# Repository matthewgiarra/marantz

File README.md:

# marantz
Knockoffs of old Marantz stereos

# Actual content
[P700 Pre-amp board](https://github.com/matthewgiarra/marantz/tree/main/2225/PE01) with schematics, PCB layout, renders, gerber files, and photos of the completed board. 

[Confluence page](https://matthewgiarra.atlassian.net/wiki/spaces/marantz/pages/33577/Gesundheit+Model+82+Stereophonic+Receiver+Requirements) (design concepts, system requirements, etc.)

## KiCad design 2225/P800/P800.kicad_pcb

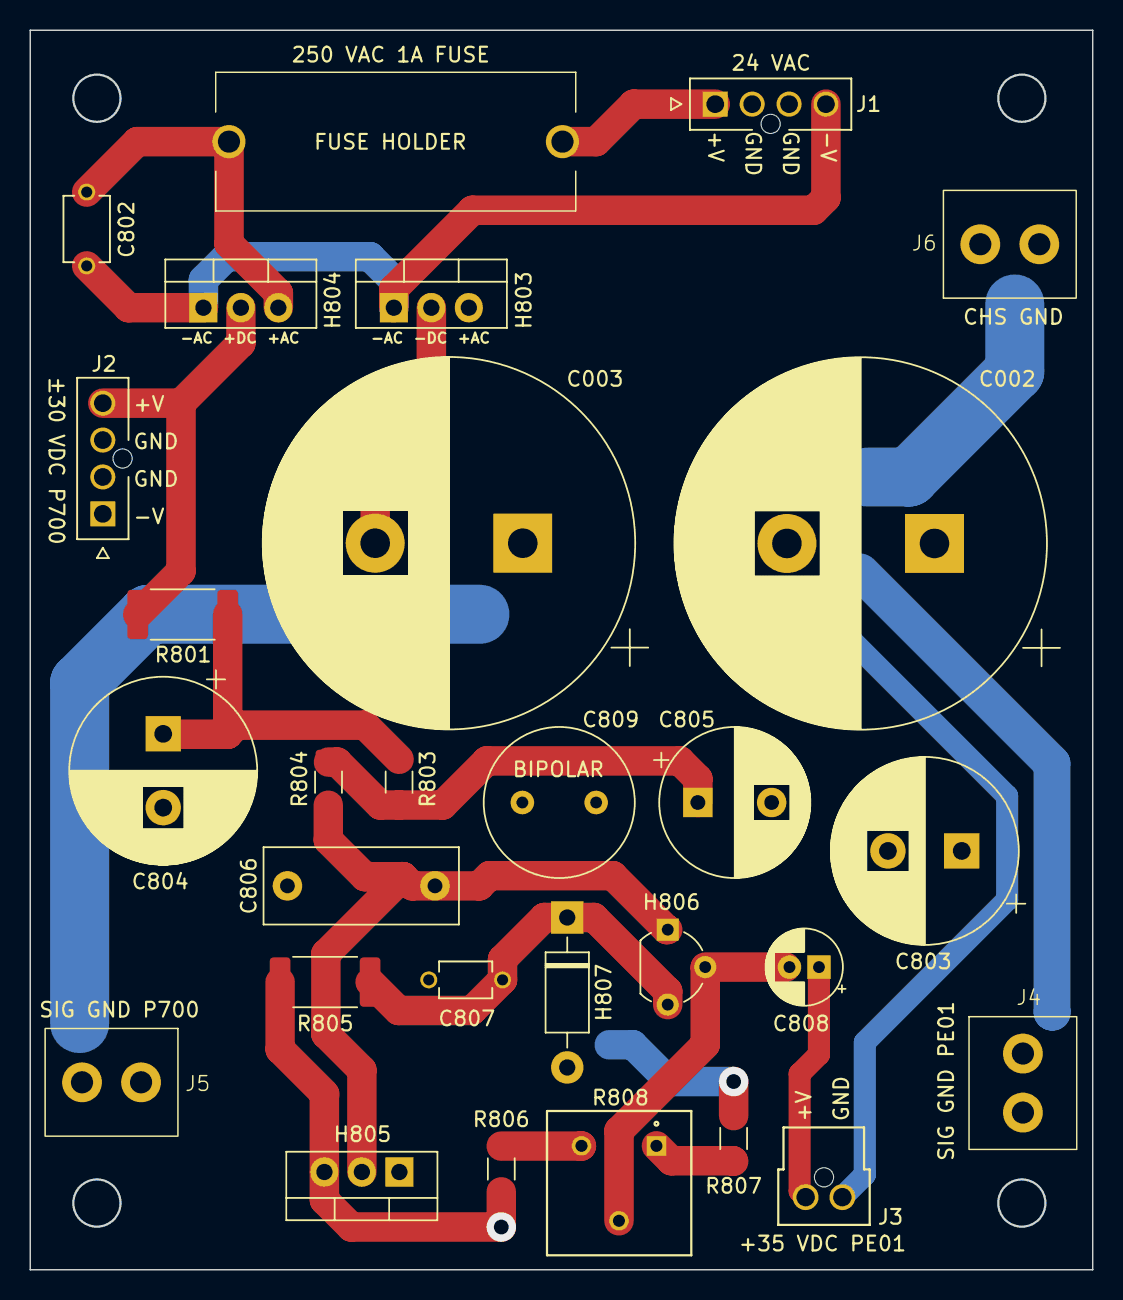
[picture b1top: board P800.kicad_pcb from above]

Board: 4 copper layers, 71.9 x 83.9 mm, 30 parts (0 on the bottom side), 14 nets.

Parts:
C002, C003: 6800u; CP_Radial_D25.0mm_P10.00mm_SnapIn
C802: 0.01u; cap_ceramic_RDER72H103K1M1H03A
C803, C804: 470u; CP_Radial_D12.5mm_P5.00mm
C805: 100u; CP_Radial_D10.0mm_P5.00mm
C806: 0.047u; C_Rect_L13.0mm_W5.0mm_P10.00mm_FKS3_FKP3_MKS4
C807: 0.04u; cap_ceramic_RCER71H473K0M1H03A
C808: 3.3u; CP_Radial_D5.0mm_P2.00mm
C809: 470u; C_Radial_D10.0mm_H20.0mm_P5.00mm
F1: Fuse 1A 250V; fuse_holder_0PTF0078P
H803: MBRF10150CTR; TO-220-3_Vertical
H804: MBRF10150CT; TO-220-3_Vertical
H805: TIP41C; TO-220-3_Vertical
H806: KSC2383; TO-92_Wide
H807: 1N4744; D_DO-41_SOD81_P10.16mm_Horizontal
HS1: Heatsink; heatsink_577202B00000G
J1, J2: Conn_01x04; molex_nanofit_4-pos_header_vert_1053091204
J3: Conn_01x02; molex_nanofit_2-pos_header_vert_1053091302
J4, J5, J6: Conn_01x01; Metz_Connect_1pos_terminal_360291
R801: 22; R_2512_6332Metric_Pad1.40x3.35mm_HandSolder
R803, R804: 1.5k; R_1206_3216Metric_Pad1.30x1.75mm_HandSolder
R805: 330; R_2512_6332Metric_Pad1.40x3.35mm_HandSolder
R806: 39k; R_1206_3216Metric_Pad1.30x1.75mm_HandSolder
R807: 36k; R_1206_3216Metric_Pad1.30x1.75mm_HandSolder
R808: TRIMPOT 5K; pot_3386F-1-502LF

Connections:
/+24VAC: F1.1, J1.1
/+30VDC_out: C002.1, C803.1, H804.2, J2.4, R801.1
/+35VDC_out: C808.1, H805.3 (E), J3.2, R805.2, R806.2
/-24VAC: C802.2, H803.1, H804.1, J1.4
/-30VDC_out: C003.2, H803.2, J2.1
/H805C_45V: C804.1, H805.1 (C), R801.2, R803.2
FBR AC +: C802.1, F1.2, H803.3, H804.3
GND: C002.2, C003.1, C803.2, C804.2, C805.2, C806.2, C807.2, C809.2, H807.2 (A), J1.2, J1.3, J2.2, J2.3, J3.1, J4.1, J5.1, J6.1, R807.1
unnamed: C805.1, R803.1, R804.2
unnamed: C806.1, H805.2 (B), H806.1 (C), R804.1
unnamed: C808.2, H806.2 (B), R808.2
unnamed: C807.1, C809.1, H806.3 (E), H807.1 (K), R805.1
unnamed: R806.1, R808.3
unnamed: R807.2, R808.1

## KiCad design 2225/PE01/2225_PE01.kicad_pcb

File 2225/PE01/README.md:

# Marantz 2225 Pre-Tone Amplifier PE-01 (pre-amp)
## Overview
This project recreates (i.e., knocks off) the [Marantz 2225](https://classicreceivers.com/marantz-2225) pre-tone amplifier (PE-01), as specified in the [Marantz 2225L service manual](https://www.manualslib.com/manual/907153/Marantz-2225l.html), using modern and readily-available components. Our custom board is designed to function as a drop-in replacement for the original device. We [selected components](https://docs.google.com/spreadsheets/d/1S8Fiy-nARGqUnUXXbVScigvOsDpP3ZsTfdl-bGImHVc/edit?usp=sharing) that meet or exceed the specifications from the service manual, which were experimentally verified by measuring values of components sourced from a vintage PE-01. When discrepancies were discovered between the service manual's component specifications and physical measurements of vintage components, we prioritized the physical measurements. The PCB layout was modified as necessary to accommodate the physical dimensions of our chosen components, and uses a four-layer PCB rather than the single layer of the original product. We used KiCad for design, and validated functionality via SPICE simulation prior to manufacturing. Quantitative characterization of the physical prototype is still in progress, but the initial subjective impression is that it sounds pretty good. 

## Components
The bill of materials/components list is [here](https://docs.google.com/spreadsheets/d/1S8Fiy-nARGqUnUXXbVScigvOsDpP3ZsTfdl-bGImHVc/edit?usp=sharing).

## KiCad renders 

## Prototype board (V1.0, March 2023)

## Original PCB

## Schematic and Layout (from [Marantz 2225L service manual](https://www.manualslib.com/manual/907153/Marantz-2225l.html))

## Notes
- CE21 and CE22 should be 3.3µF, not 33µF as they're listed in the service manual.
- CE23 and CE24 are biopolar capacitors, which the service manual does not appear to indicate. 
- The first prototype board substituted the specified 7.5K resistors RE13 and RE14 with 4.7K 1% components. The reason for the substitution was to mitigate clipping observed at higher volume levels (i.e., lower input attenuation) of aux input from a Macbook headphone jack, which was about 1.5VPP.

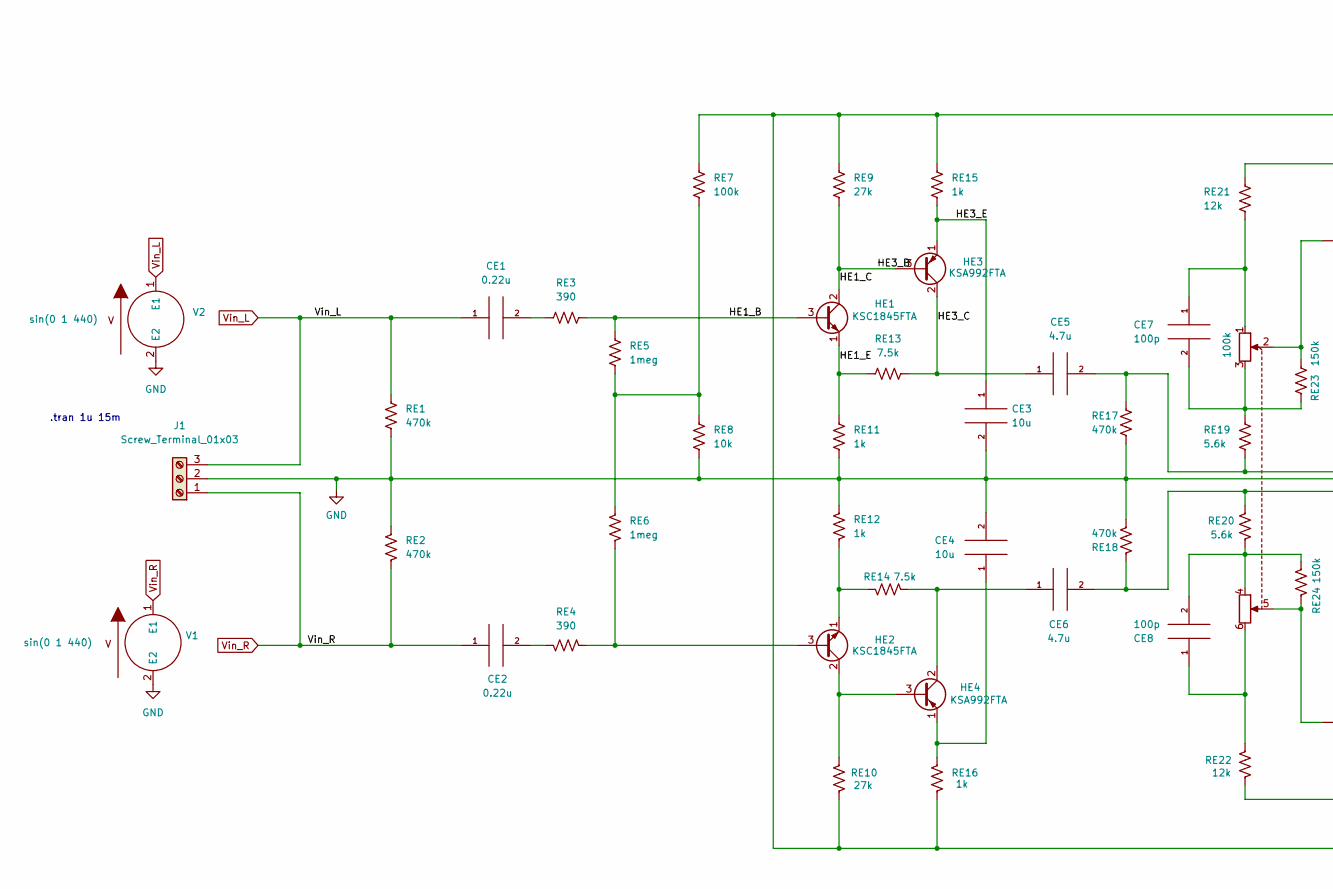
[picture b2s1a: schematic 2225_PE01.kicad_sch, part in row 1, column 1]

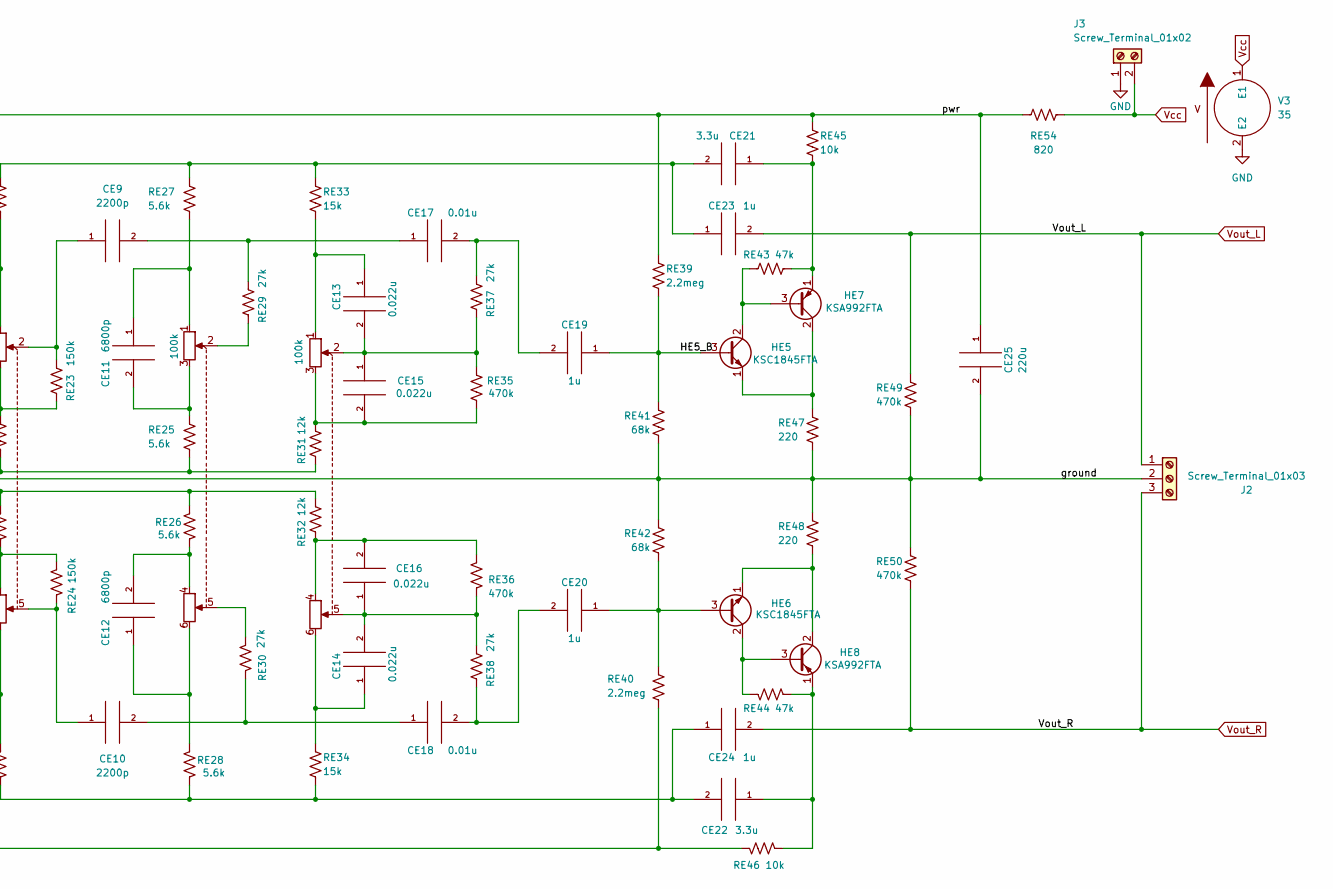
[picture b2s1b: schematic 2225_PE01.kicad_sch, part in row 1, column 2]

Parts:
CE1, CE2: 0.22u; C_Rect_L16.5mm_W4.7mm_P15.00mm_MKT
CE3, CE4: 10u; CP_Radial_D6.3mm_P2.50mm
CE5, CE6: 4.7u; CP_Radial_D5.0mm_P2.50mm
CE7, CE8: 100p; C_Disc_D7.0mm_W2.5mm_P5.00mm
CE9, CE10: 2200p; C_Rect_L7.2mm_W3.5mm_P5.00mm_FKS2_FKP2_MKS2_MKP2
CE11, CE12: 6800p; C_Rect_L7.2mm_W3.5mm_P5.00mm_FKS2_FKP2_MKS2_MKP2
CE13, CE14, CE15, CE16: 0.022u; C_Rect_L10.0mm_W4.0mm_P7.50mm_FKS3_FKP3
CE17, CE18: 0.01u; C_Rect_L9.0mm_W3.2mm_P7.50mm_MKT
CE19, CE20: 1u; CP_Radial_D5.0mm_P2.50mm
CE21, CE22: 3.3u; CP_Radial_D6.3mm_P2.50mm
CE23: 1u; C_Radial_D6.3mm_H11.0mm_P3.50mm
CE24: 1u; C_Radial_D6.3mm_H11.0mm_P2.50mm
CE25: 220u; CP_Radial_D10.0mm_P5.00mm
HE1, HE2, HE5, HE6: KSC1845FTA; TO-92_Inline
HE3, HE4, HE7, HE8: KSA992FTA; TO-92_Inline
J1, J2: Screw_Terminal_01x03; Molex_Eurostyle_39357-0003_1x03_P3.5mm_Horizontal
J3: Screw_Terminal_01x02; Molex_Eurostyle_39357-0002_1x02_P3.5mm_Horizontal
RE1, RE2, RE17, RE18, RE35, RE36, RE49, RE50: 470k; R_Axial_DIN0309_L9.0mm_D3.2mm_P12.70mm_Horizontal
RE3, RE4: 390; R_Axial_DIN0309_L9.0mm_D3.2mm_P12.70mm_Horizontal
RE5, RE6: 1meg; R_Axial_DIN0309_L9.0mm_D3.2mm_P5.08mm_Vertical
RE7: 100k; R_Axial_DIN0309_L9.0mm_D3.2mm_P12.70mm_Horizontal
RE8, RE45, RE46: 10k; R_Axial_DIN0309_L9.0mm_D3.2mm_P12.70mm_Horizontal
RE9, RE10, RE29, RE30, RE37, RE38: 27k; R_Axial_DIN0309_L9.0mm_D3.2mm_P12.70mm_Horizontal
RE11: 1k; R_Axial_DIN0309_L9.0mm_D3.2mm_P20.32mm_Horizontal
RE12, RE15, RE16: 1k; R_Axial_DIN0309_L9.0mm_D3.2mm_P12.70mm_Horizontal
RE13, RE14: 7.5k; R_Axial_DIN0309_L9.0mm_D3.2mm_P12.70mm_Horizontal
RE19, RE20, RE25, RE26, RE27, RE28: 5.6k; R_Axial_DIN0309_L9.0mm_D3.2mm_P12.70mm_Horizontal
RE21, RE22, RE31, RE32: 12k; R_Axial_DIN0309_L9.0mm_D3.2mm_P12.70mm_Horizontal
RE23, RE24: 150k; R_Axial_DIN0309_L9.0mm_D3.2mm_P12.70mm_Horizontal
RE33, RE34: 15k; R_Axial_DIN0309_L9.0mm_D3.2mm_P12.70mm_Horizontal
RE39, RE40: 2.2meg; R_Axial_DIN0309_L9.0mm_D3.2mm_P12.70mm_Horizontal
RE41, RE42: 68k; R_Axial_DIN0309_L9.0mm_D3.2mm_P12.70mm_Horizontal
RE43, RE44: 47k; R_Axial_DIN0309_L9.0mm_D3.2mm_P12.70mm_Horizontal
RE47, RE48: 220; R_Axial_DIN0309_L9.0mm_D3.2mm_P12.70mm_Horizontal
RE51, RE52, RE53: 100k; Potentiometer_Marantz_RM0104005
RE54: 820; R_Axial_DIN0309_L9.0mm_D3.2mm_P12.70mm_Horizontal
V1, V2: 0
V3: 35

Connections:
/HE1_B: HE1.3 (B), RE3.2, RE5.2
/HE1_C: HE1.2 (C), HE3.3 (B), RE9.1
/HE1_E: HE1.1 (E), RE11.2, RE13.1
/HE3_C: CE5.1, HE3.2 (C), RE13.2
/HE3_E: CE3.1, HE3.1 (E), RE15.1
/HE5_B: CE19.1, HE5.3 (B), RE39.1, RE41.2
/pwr: CE25.1, RE7.2, RE9.2, RE10.2, RE15.2, RE16.2, RE39.2, RE40.1, RE45.2, RE46.1, RE54.1
GND: CE3.2, CE4.2, CE25.2, J1.2, J2.2, J3.1, RE1.1, RE2.1, RE8.1, RE11.1, RE12.1, RE17.1, RE18.1, RE41.1, RE42.2, RE47.1, RE48.2, RE49.1, RE50.2, V1.2 (E2), V2.2 (E2), V3.2 (E2)
unnamed: CE1.2, RE3.1
unnamed: CE2.2, RE4.1
unnamed: CE4.1, HE4.1 (E), RE16.1
unnamed: CE5.2, RE17.2, RE19.1, RE25.1, RE31.1
unnamed: CE6.1, HE4.2 (C), RE14.2
unnamed: CE6.2, RE18.2, RE20.1, RE26.1, RE32.2
unnamed: CE7.1, RE21.1, RE51.1
unnamed: CE7.2, RE19.2, RE23.1, RE51.3
unnamed: CE8.1, RE22.1, RE51.6
unnamed: CE8.2, RE20.2, RE24.1, RE51.4
unnamed: CE9.1, RE23.2, RE51.2
unnamed: CE10.1, RE24.2, RE51.5
unnamed: CE10.2, CE18.1, RE30.2
unnamed: CE11.1, RE27.1, RE52.1
unnamed: CE11.2, RE25.2, RE52.3
unnamed: CE12.1, RE28.1, RE52.6
unnamed: CE12.2, RE26.2, RE52.4
unnamed: CE13.1, RE33.1, RE53.1
unnamed: CE13.2, CE15.1, RE35.2, RE37.1, RE53.2
unnamed: CE14.1, RE34.2, RE53.6
unnamed: CE14.2, CE16.1, RE36.2, RE38.2, RE53.5
unnamed: CE15.2, RE31.2, RE35.1, RE53.3
unnamed: CE16.2, RE32.1, RE36.1, RE53.4
unnamed: CE9.2, CE17.1, RE29.2
unnamed: CE17.2, CE19.2, RE37.2
unnamed: CE18.2, CE20.2, RE38.1
unnamed: CE20.1, HE6.3 (B), RE40.2, RE42.1
unnamed: CE21.1, HE7.1 (E), RE43.2, RE45.1
unnamed: CE21.2, CE23.1, RE21.2, RE27.2, RE33.2
unnamed: CE22.1, HE8.1 (E), RE44.2, RE46.2
unnamed: CE22.2, CE24.1, RE22.2, RE28.2, RE34.1
unnamed: HE2.1 (E), RE12.2, RE14.1
unnamed: HE2.2 (C), HE4.3 (B), RE10.1
unnamed: HE2.3 (B), RE4.2, RE6.2
unnamed: HE5.1 (E), HE7.2 (C), RE47.2
unnamed: HE5.2 (C), HE7.3 (B), RE43.1
unnamed: HE6.1 (E), HE8.2 (C), RE48.1
unnamed: HE6.2 (C), HE8.3 (B), RE44.1
unnamed: RE5.1, RE6.1, RE7.1, RE8.2
unnamed: RE29.1, RE52.2
unnamed: RE30.1, RE52.5
Vcc: J3.2, RE54.2, V3.1 (E1)
Vin_L: CE1.1, J1.3, RE1.2, V2.1 (E1)
Vin_R: CE2.1, J1.1, RE2.2, V1.1 (E1)
Vout_L: CE23.2, J2.1, RE49.2
Vout_R: CE24.2, J2.3, RE50.1

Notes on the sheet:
.tran 1u 15m

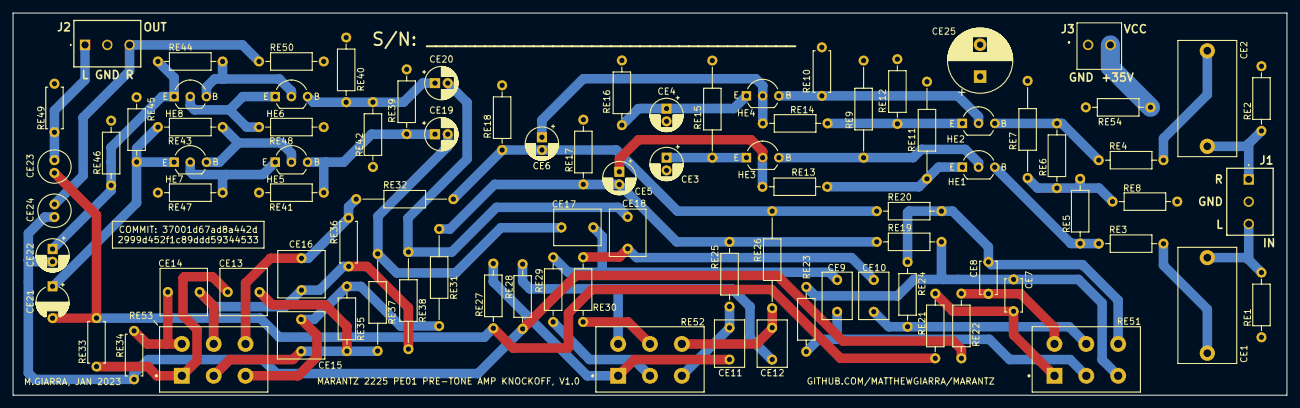
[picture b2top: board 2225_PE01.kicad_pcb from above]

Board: 4 copper layers, 200.0 x 60.0 mm, 90 parts (0 on the bottom side), 54 nets.

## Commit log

2022-10-23 Added .gitignore
2022-10-23 Initial commit of KiCad files. 2225 PE01 schematic drafted and PCB component initial placement done.
2022-10-23 Added rough board outline to PCB (dimensions are wrong).
2022-11-10 Changed footprints of RE5 and RE6 from vertical resistors to horizontal
2022-11-10 Updated footprint symbols types to match real board (squiggly resistors, etc). Also updated annotations for RE51, RE52, RE53
2022-11-10 Cleaned up some traces.
2022-11-10 Made more PCB footprints to match schematic symbols. Also aligned component text in PCB silkscreen.
2022-11-10 Updated footprints of CE9 - CE12. Changed some trace widths to 0.5mm
2022-11-10 Deleted some superfluous traces
2022-11-10 Moved some silkscreen text around
2022-11-10 Changed transistor footprints to common packaging spec. Also fixed some trace intersections.
2022-11-10 Rerouted traces and moved components to tie together ground plane
2022-11-10 Cleaned up traces and made most of them 1mm
2022-11-10 Spaced out some components
2022-11-10 Minor trace moves
2022-11-10 Added ground plane.
2022-11-10 Set PCB component positions to match holes on donor board
2022-11-10 Fixed CE1, which was upside down on pcb layout
2022-11-10 Rerouted components and traces to consolidate ground plane
2022-11-10 Moved some traces around to make room around components
2022-11-10 Changed some capacitor footprints to match real components
2022-11-10 Changed footprint of CE13 and CE14 to real WIMA caps.
2022-11-10 Re-routed a trace
2022-11-10 Fixed short circuit across RE8. Added traces. Still need ground plane.
2022-11-10 Repositioned some components so that ground plane actually tied grounds together
2022-11-10 Updated capacitor footprints to represent available components
2022-11-10 Widened some choke points on the ground plane
2022-11-10 Extended ground plane.
2022-11-10 Added 2225/PE01/README.md
2022-11-15 Updated footprints of resitors and caps to match final component selections
2022-11-15 Moved components and updated fooprints to mitigate design rules checker warnings
2022-12-27 Got spice simulation working. Put all component libraries in PE01.lib
2023-01-03 Changed and re-positioned pot footprints. Left traces as-is, so this commit is a WIP.
2023-01-16 Made board 4 layers and re-routed all the traces.
2023-01-17 Updated design rules and some footprints to match EasyEDA requirements.
2023-01-17 Cropped footprints that overlapped board edge; moved some text.
2023-01-17 Added textbox with hash of previous commit to PCB silkscreen
2023-01-18 Added silkscreen text to label terminal block connections; moved components to accommodate text.
2023-01-23 Updated names of front and back copper layers to not include (L) and (R)
2023-01-23 Updated 2225 PE01 silk screen to reflect board as-released for mfg. Added gerberfiles that were released to manufacturer (JLCPCB order Y3-5424344A).
2023-05-05 Disabled terminal blocks in spice sim of 2225 PE01 because there was no spice model defined for them and the sim wouldnt run
2023-05-20 Created 2225/P800 kicad project
2023-06-08 Created initial P800 schematic
2023-06-12 Added model files for Zener diode, transistors, and trim pot
2023-06-13 Created diode bridge components (P800 H801:H804) in project-specific symbol library; updated schematic to include H803 & H804
2023-06-15 Added model file (subckt) for diode bridges P800 H803 & H804
2023-06-15 Resolved spice not finding diode model by adding D prefix to model name in D1N4744A.lib
2023-06-21 Changed feedback transistor P800/H806 to KSC2373; adjusted values of voltage divider in feedback circuit of P800
2023-07-17 Replaced global labels with hierarchical labels, and removed sources and loads, in 2225_PE01.kicad_sch (in prep. for integrating into multi-sheet schematic)
2023-07-17 Consolidated spice model files (.lib) in models directory. Specified spice paths relative to {KIPRJMOD} env variable.
2023-07-17 Created 2225 system schematic
2023-07-17 added *.raw to .gitignore (LTspice results files?)
2023-08-25 Added models/2225/2225.lib for system-level models; included 120VAC to 24/48VAC transformer.
2023-10-29 completed P800 schematic
2023-10-30 Added hierarchical labels to 2225/PE01.kicad_sch
2023-11-01 Connected transformer to P800 in 2225.kicad_sch; changed transformer model resistances in 2225.lib
2023-11-01 Connected P800 (DC supply) to PE01 tone board, audio source to PE01, and PE01 to dummy P700 main amplifier. Changed some hierarchical label names in multiple schematics.
2023-11-01 Added dummy power inputs to P700 block in 2225.kicad_sch (system block diagram)
2023-11-09 Initial system block diagram of 2225
2023-11-09 Committing some changes to 2225_PE01.kicad_sch, but I dont really know why the file changed.
2024-10-02 Updated terminal connectors in 2225/P800/P800.kicad_sch
2024-10-03 Aligned 2225/P800 schematic elements to grid so ERC would run without warnings. Deconflicted net names. Fixed warning about GND having been modified in PWR library.
2024-10-03 Made and populated 2225/P800/3dmodels and libs. Created project footprint library for 2225/P800. Added molex connector foorptints to 2225/P800 library.
2024-11-04 Changed molex block connectors for all VDC_out to SMA right angle THT. Aligned schematic to 50.0 mil grid to fix electrical rules checker warnings.
2024-11-23 Added footprints and 3D models for all components; assigned footprints to all components; populated PCB file with all footprints
2024-11-26 Completed initial P800 board layout.
2024-11-27 Added screw mounting holes to 2225/P800 PCB
2024-11-28 Replaced custom capacitor footprints with kicad standard footprints
2024-11-28 Replaced star ground pattern with single ground plane
2024-11-29 Made P800 PCB smaller
2025-07-23 Redesigned P800 layout
2025-07-24 Changed molex connectors on P800 pcb from horizontal to vertical plug direction components
2025-07-24 Upgraded to Kicad 9 format
